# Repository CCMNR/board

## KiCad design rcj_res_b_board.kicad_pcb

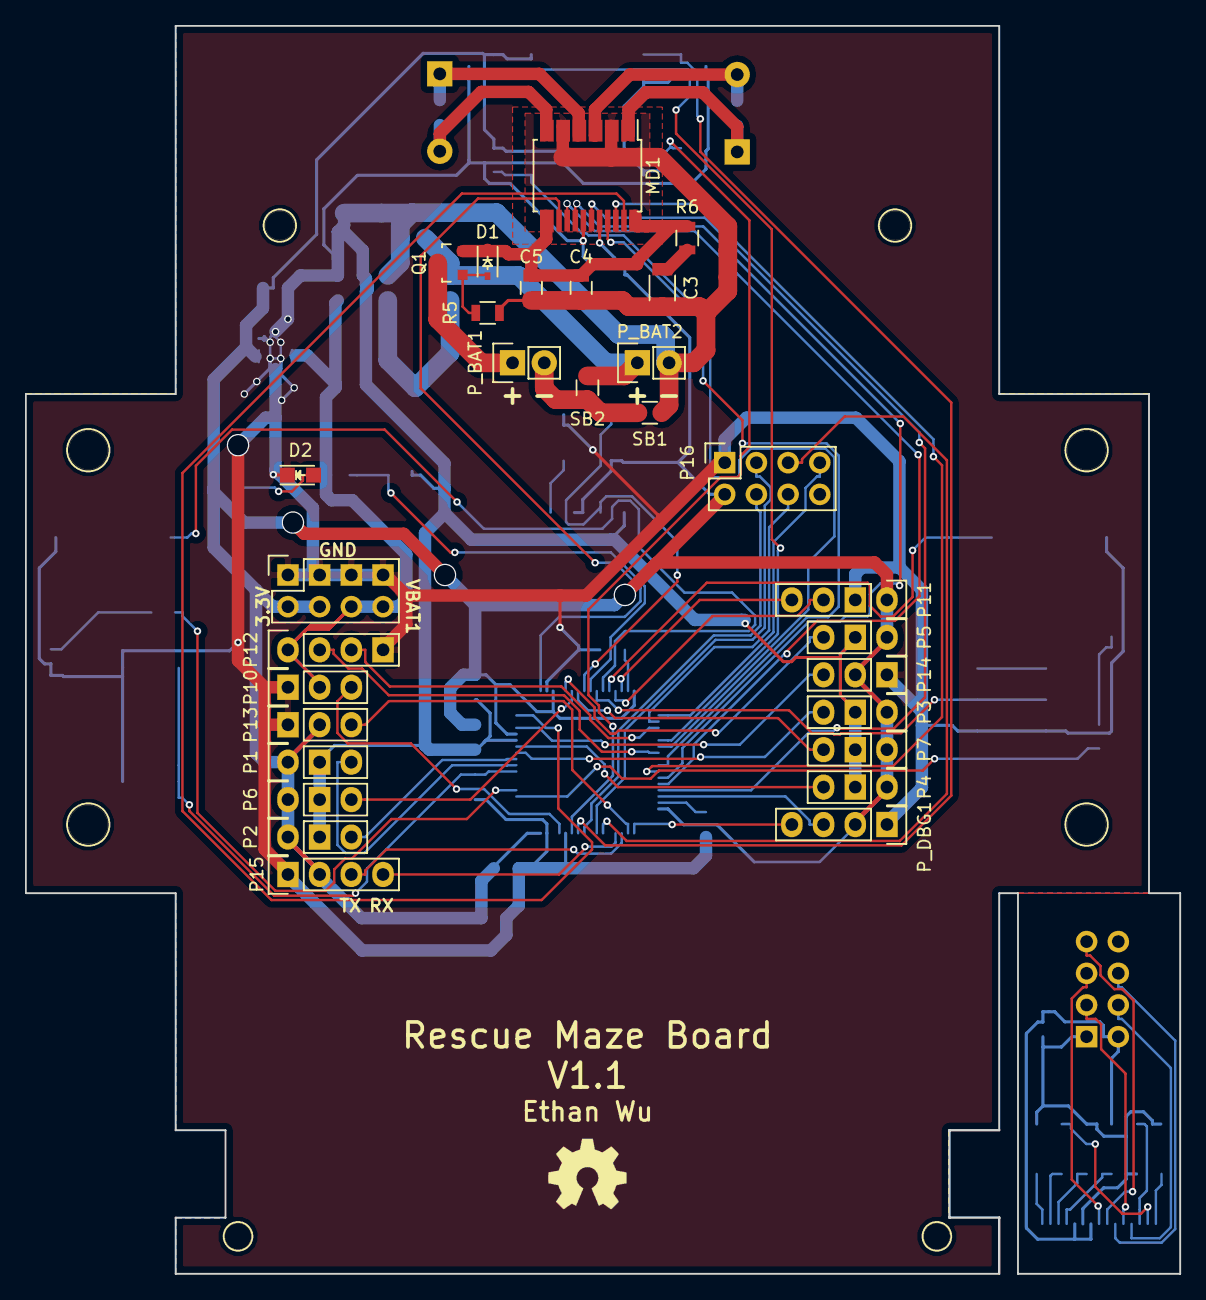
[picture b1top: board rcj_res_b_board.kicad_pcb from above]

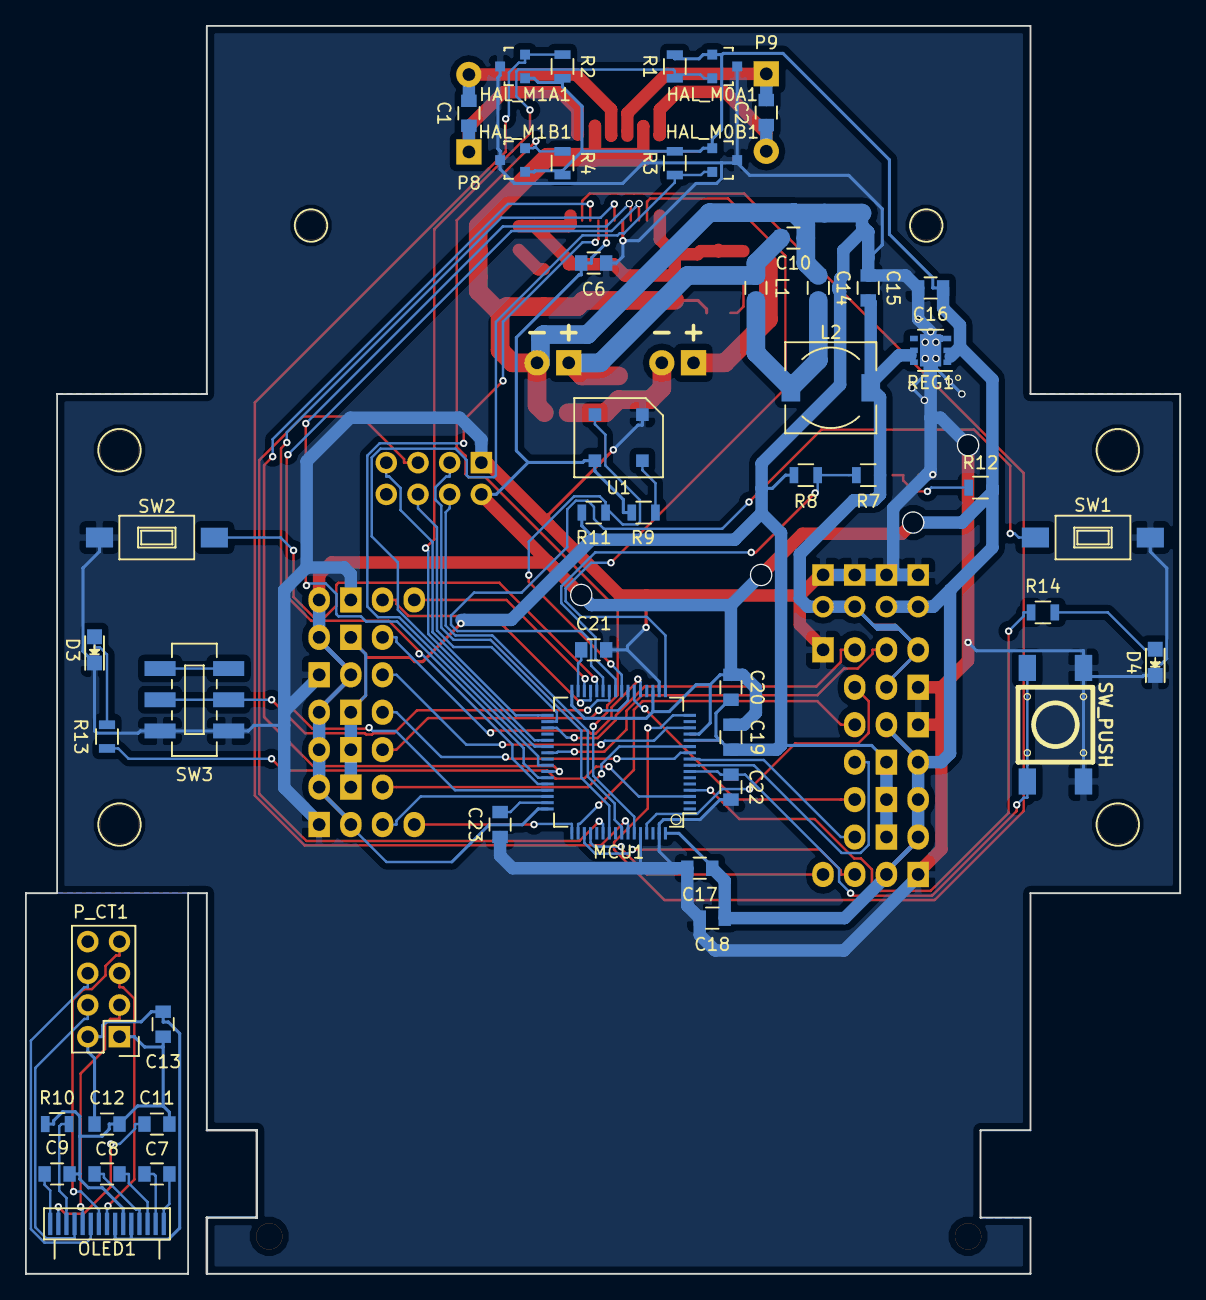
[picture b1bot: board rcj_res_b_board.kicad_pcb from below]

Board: 2 copper layers, 92.5 x 100.0 mm, 93 parts (54 on the bottom side), 80 nets.

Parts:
C1, C2: 3.3nF; C_0805
C3: 10uF; C_1206
C4, C6, C10, C18, C20: 0.1uF; C_0805
C5: 0.47uF; C_0805
C7, C8, C12, C13, C14: 1uF; C_0805
C9, C11, C15, C16, C17, C19, C21, C23: 10uF; C_0805
C22: 0.01uF; C_0805
D1: 6.8V; SOD-323
D2, D3, D4: LED; LED-0805
G001: LOGO; OSH_LOGO
HAL_M0A1, HAL_M0B1, HAL_M1A1, HAL_M1B1: AH1751; SOT-23
HOLE1, HOLE2, HOLE3, HOLE4, HOLE5, HOLE6, HOLE7, HOLE8: 1pin
L1: L_Small; C_0805
L2: L_Small; Choke_SMD_7.3x7.3_H3.5
MCU1: STM32F405RG; LQFP-64_10x10mm_Pitch0.5mm
MD1: TB6612FNG; SSOP-24_5.3x8.2mm_Pitch0.65mm
NT1, NT2: Net_Tie; NET_TIE_1.5mm
NT3, NT4: Net_Tie; NET_TIE_1mm
OLED1: UG-2832HSWEG04
P1, P2, P3, P4: GP2Y0A41SK0F; Socket_Strip_Straight_1x03
P5, P6, P7: GP2Y0A21YK; Socket_Strip_Straight_1x03
P8, P9: CONN_01X02; Socket_Strip_Straight_1x02
P10: SERVO0; Socket_Strip_Straight_1x03
P11: MPU9250; Socket_Strip_Straight_1x04
P12: PING0; Socket_Strip_Straight_1x04
P13, P14: CONN_01X03; Socket_Strip_Straight_1x03
P15: CONN_01X04; Socket_Strip_Straight_1x04
P16: CONN_02X04; Socket_Strip_Straight_2x04
P_BAT1, P_BAT2: CONN_01X02; Pin_Header_Straight_1x02
P_CT1: CONN_02X04; Pin_Header_Straight_2x04
P_DBG1: CONN_01X04; Socket_Strip_Straight_1x04
P_PWR1: CONN_02X04; Socket_Strip_Straight_2x04
Q1: Q_PMOS_GSD; SOT-23
R1, R2, R3, R4, R7, R8, R11: 10k; R_0805
R5: 100k; R_0805
R6: 1; R_0805
R9: 100; R_0805
R10: 390k; R_0805
R12, R13, R14: 1k; R_0805
REG1: LD39200PU; DFN-6-1EP_3x3mm_Pitch0.95mm
SB1, SB2: 0; R_0805
SW1, SW2: SW_PUSH; SW_SPST_FSMSM
SW3: SWITCH_INV; JS202011SCQN
SW_RST1: SW_PUSH; Switch_FSM_JSM
U1: OPB733TR

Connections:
/3.3V: C6.2, C16.1, C17.1, C18.1, C19.1, C20.1, HAL_M0A1.1, HAL_M0B1.1, HAL_M1A1.1, HAL_M1B1.1, MCU1.13, MCU1.19, MCU1.32, MCU1.48, MCU1.64, MD1.20, P1.1, P2.1, P3.1, P4.1, P5.1, P6.1, P7.1, P11.1, P13.2, P14.2, P15.2, P16.2, P_DBG1.2, P_PWR1.2, P_PWR1.4, R1.1, R2.1, R3.1, R4.1, R9.1, R12.1, REG1.1, REG1.2, U1.3
/I2C_SCL: MCU1.29, P11.3
/I2C_SDA: MCU1.30, P11.4
/IR_L_F: MCU1.21, P5.3
/IR_L_L: MCU1.22, P6.3
/IR_L_R: MCU1.23, P7.3
/IR_S_LB: MCU1.9, P2.3
/IR_S_LF: MCU1.8, P1.3
/IR_S_RB: MCU1.11, P4.3
/IR_S_RF: MCU1.10, P3.3
/LED_USR1: MCU1.3, R13.1
/LED_USR2: MCU1.4, R14.1
/LS_FLOOR: MCU1.24, R11.1, U1.2
/M0_ENC_A: HAL_M0A1.2, MCU1.37, R1.2
/M0_ENC_B: HAL_M0B1.2, MCU1.38, R3.2
/M1_ENC_A: HAL_M1A1.2, MCU1.58, R2.2
/M1_ENC_B: HAL_M1B1.2, MCU1.59, R4.2
/MD_AIN1: MCU1.41, MD1.21
/MD_AIN2: MCU1.42, MD1.22
/MD_APWM: MCU1.16, MD1.23
/MD_BIN1: MCU1.43, MD1.17
/MD_BIN2: MCU1.44, MD1.16
/MD_BPWM: MCU1.17, MD1.15
/MD_STBY: MCU1.45, MD1.19
/MODE_SEL: MCU1.26, SW3.2
/MOSI: MCU1.57, P16.4
/OLED_Circuitry/3.3V: C12.1, C13.1, OLED1.5, OLED1.7, P_CT1.2
/OLED_Circuitry/D-C: OLED1.10, P_CT1.6
/OLED_Circuitry/GND: C9.2, C11.2, C12.2, C13.2, OLED1.6, P_CT1.1, R10.1
/OLED_Circuitry/MOSI: OLED1.12, P_CT1.4
/OLED_Circuitry/RST: OLED1.9, P_CT1.7
/OLED_Circuitry/SCLK: OLED1.11, P_CT1.3
/OLED_Circuitry/SS: OLED1.8, P_CT1.5
/OLED_D-C: MCU1.34, P16.6
/OLED_RST: MCU1.33, P16.7
/OLED_SS: MCU1.54, P16.5
/PING0_ECHO: MCU1.35, P12.3
/PING0_TRIG: MCU1.39, P12.2
/SCLK: MCU1.55, P16.3
/SERVO0_PWM: MCU1.61, P10.3
/SWCLK: MCU1.49, P_DBG1.4
/SWDIO: MCU1.46, P_DBG1.3
/SW_USR1: MCU1.27, SW1.1
/SW_USR2: MCU1.28, SW2.1
/TEMP0_PWM: MCU1.50, P13.3
/TEMP1_PWM: MCU1.14, P14.3
/UART_RX: MCU1.52, P15.4
/UART_TX: MCU1.51, P15.3
/VBAT1: C15.1, L2.2, P10.2, P12.1, P_PWR1.6, P_PWR1.8, R7.1, REG1.5, REG1.6
/VBAT_MON: MCU1.25, R7.2, R8.1
GND: C10.2, C14.2, NT1.1, NT2.1, P_BAT2.2, SB1.1
GNDA: C19.2, C20.2, MCU1.12, NT4.2, P1.2, P2.2, P3.2, P4.2, P5.2, P6.2, P7.2, R8.2, R11.2
GNDD: C6.1, C15.2, C16.2, C17.2, C18.2, C21.2, C22.2, C23.2, D2.1, D3.1, D4.1, HAL_M0A1.3, HAL_M0B1.3, HAL_M1A1.3, HAL_M1B1.3, MCU1.18, MCU1.60, MCU1.63, MD1.18, NT3.2, P10.1, P11.2, P12.4, P13.1, P14.1, P15.1, P16.1, P_DBG1.1, P_PWR1.1, P_PWR1.3, P_PWR1.5, P_PWR1.7, REG1.3, REG1.7, SW1.2, SW2.2, SW3.1, SW_RST1.2, U1.1
GNDPWR: C3.2, C4.2, C5.2, MD1.3, MD1.4, MD1.9, MD1.10, NT1.2, R5.2
unnamed: C1.1, MD1.1, MD1.2, P8.1
unnamed: C1.2, MD1.5, MD1.6, P8.2
unnamed: C2.1, MD1.11, MD1.12, P9.2
unnamed: C2.2, MD1.7, MD1.8, P9.1
unnamed: C3.1, R6.2
unnamed: C4.1, C5.1, D1.1, MD1.13, MD1.14, MD1.24, Q1.2, R6.1
unnamed: C7.1, OLED1.1
unnamed: C7.2, OLED1.2
unnamed: C8.1, OLED1.3
unnamed: C8.2, OLED1.4
unnamed: C9.1, OLED1.15
unnamed: C10.1, L1.1, P_BAT2.1, SB2.1
unnamed: C11.1, OLED1.14
unnamed: C14.1, L1.2, L2.1
unnamed: C21.1, MCU1.31
unnamed: C22.1, MCU1.7, SW_RST1.1
unnamed: C23.1, MCU1.47
unnamed: D1.2, Q1.1, R5.1
unnamed: D2.2, R12.2
unnamed: D3.2, R13.2
unnamed: D4.2, R14.2
unnamed: NT2.2, NT3.1, NT4.1
unnamed: OLED1.13, R10.2
unnamed: P_BAT1.2, SB1.2, SB2.2
unnamed: R9.2, U1.4
VCC: P_BAT1.1, Q1.3

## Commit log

2015-12-19 Initial commit
    Board and schematic created
2015-12-19 Moved SMD components to back
    Moving components to back to free up space -
    fewer physical obstacles / limitations
2015-12-19 General updates / improvements
    Added bottom-facing IR light sensor
    Changed motor driver from Pololu boards to TB6612FNG
    Added OLED mount
    Expanded front of board to mount motors
    Added misc headers and headers for other sensors
    Motor terminals are now exposed pads and not THT pin headers
2015-12-26 Minor fixes
    Connected previously disconnected serial port (in schematic)
    Added labels
    Added missing cutout in side of board
    Adjusted mounting hole positions
2015-12-26 Prep for fabrication
    Added ground planes
    Added switches
    Added cutoffs for mounting sensors
    Added additional silkscreen info
2015-12-26 Moved hall-effect sensors
    Connected serial port in netlist (netlist update)
    Added pcbnew autosaves to gitignore
2015-12-27 Power rewire
    Added reverse current protection on motor driver
    Switched most 5V devices to 3.3V
    3.3V power now comes from tapping one battery (not both)
2015-12-29 Changed power supply
    Now using one 3.3V ULDO regulator
    Removed 5V power (ping powered directly from battery)
    Added filtering network (chokes and caps)
    Added 2 indicator LEDs
    Fixed EVQPL* button footprints
    Added pcbnew lib table
2015-12-29 Preliminary layout
    Changed push-button footprints
2015-12-29 Moved motor driver RCP circuit to front
    Rearranged other components to make space
2015-12-29 Moved OLED to cut-off board
    Removed PIR cutoffs (no longer needed)
2015-12-29 Initial routing
    Added solder bridges
    Added missing library
2015-12-30 Changed servo to use VBAT power
    Also increased size of net-ties
2015-12-30 More preliminary routing
2016-01-01 Flipped cutoff around
    Changed copper fills to have no net
2016-01-01 Moved footprints around to match physical
    Hall-effect sensors and motor connectors moved towards center
    Rotated one of the motor connectors
    Fixed overlapping silkscreens
2016-01-01 Re-arranged headers
    Resized some screw holes
2016-01-01 Changed drill hole size and moved decoupling cap
    Shrunk drill hole for mounting dropper (2.3mm -> 2.1mm)
    Moved motor driver decoupling cap closer to motor driver
    Fixed incorrectly placed LED
2016-01-01 Power routing & prep for autoroute
    Moved some components to make routing power easier (net ties)
2016-01-02 Changed grounds
    Servo now uses digital ground
    Battery monitor uses analog ground
    Moved P_PWR1's 3.3V (used for debugging) to debug header
    P_PWR2 -> P_PWR1
2016-01-02 Re-routed power
    Removed unnecessary wiring that wasn't power (to let autorouter route instead)
    Misc fixes
2016-01-03 Routed
    Fixed offset / misplaced zone outline
2016-01-03 Added thermal vias
    Final cleanup
2016-02-01 Changed resistor value
    Changed value on phototransistor of light sensor to get higher dynamic range in readings
    (tested)
2016-08-19 Change resistor value
    80 ohm resistor for floor light sensor was replaced by 100 ohm on boards, update schematics to match
2017-06-26 Revert PCB board KiCad version
